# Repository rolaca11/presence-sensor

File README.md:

# Presence Sensor

A compact Zigbee presence sensor based on the Texas Instruments CC2340R5 microcontroller and a UART-connected mmWave radar module. Detects human presence and reports occupancy over Zigbee, with configurable detection parameters.

## Features

- **CC2340R5** - Low-power Zigbee microcontroller
- **mmWave radar sensor** - UART-connected presence detection module with configurable range, sensitivity, and latency
- **Zigbee End Device** - Occupancy Sensing cluster with custom attributes for remote sensor configuration
- **USB-C** - Power supply
- **Programming header** - 3-pin JST-SH connector for flashing firmware (compatible with Raspberry Pi Debug Probe)
- **3.3V LDO** - XC6206 voltage regulator
- **Factory reset button** - Hold on boot to clear network credentials
- **32.768 kHz & 48 MHz crystals** - For accurate timing and radio operation

## Project Structure

```
presence-sensor/
├── pcb/                    # KiCad 9 project files
│   ├── production/         # Manufacturing files (Gerbers, BOM, positions)
│   ├── footprints.pretty/  # Custom footprints
│   └── 3dmodels/           # 3D models for components
├── firmware/               # Zigbee firmware (CCS project, TI SimpleLink SDK)
├── enclosure/              # 3D printable enclosure (STEP + STL files)
└── LICENSE
```

## Firmware

The firmware is a Code Composer Studio project built on the TI SimpleLink Low Power F3 SDK. It implements a Zigbee End Device that:

- Reads presence data from the mmWave sensor over UART (9600 baud)
- Reports occupancy via the standard **Occupancy Sensing** cluster
- Sends **On/Off** commands to bound devices when presence state changes
- Exposes custom Zigbee attributes (`0xE000`–`0xE008`) for configuring the sensor remotely:

| Attribute | ID | Type | Description |
|-|-|-|-|
| Range Min | `0xE000` | uint16 | Minimum detection range (cm) |
| Range Max | `0xE001` | uint16 | Maximum detection range (cm) |
| Trigger Range | `0xE002` | uint16 | Trigger detection range (cm) |
| Trigger Sensitivity | `0xE003` | uint8 | Trigger sensitivity (0–9) |
| Keep Sensitivity | `0xE004` | uint8 | Keep sensitivity (0–9) |
| Trigger Delay | `0xE005` | uint8 | Trigger delay (x10ms) |
| Keep Timeout | `0xE006` | uint16 | Keep timeout (x500ms) |
| IO Polarity | `0xE007` | uint8 | Output pin polarity |
| Micromotion | `0xE008` | bool | Micromotion detection enable |

### Building

1. Install [Code Composer Studio](https://www.ti.com/tool/CCSTUDIO) v12.7+
2. Install the [SimpleLink Low Power F3 SDK](https://www.ti.com/tool/SIMPLELINK-LOWPOWER-SDK) v9.14+
3. Import the `firmware/` directory as a CCS project
4. Build and flash via the 3-pin SWD header using a compatible debug probe

## Manufacturing

Production files for PCB fabrication are located in `pcb/production/`:
- Gerber files (zipped)
- Bill of Materials (`bom.csv`)
- Pick and place positions (`positions.csv`)

The BOM includes LCSC part numbers for assembly at JLCPCB or similar services.

## Requirements

- [KiCad 9](https://www.kicad.org/) to view/edit the PCB design
- [Code Composer Studio](https://www.ti.com/tool/CCSTUDIO) v12.7+ to build the firmware
- [SimpleLink Low Power F3 SDK](https://www.ti.com/tool/SIMPLELINK-LOWPOWER-SDK) v9.14+
- 3D printer for the enclosure (optional)

## License

This project is licensed under the MIT License - see the [LICENSE](LICENSE) file for details.

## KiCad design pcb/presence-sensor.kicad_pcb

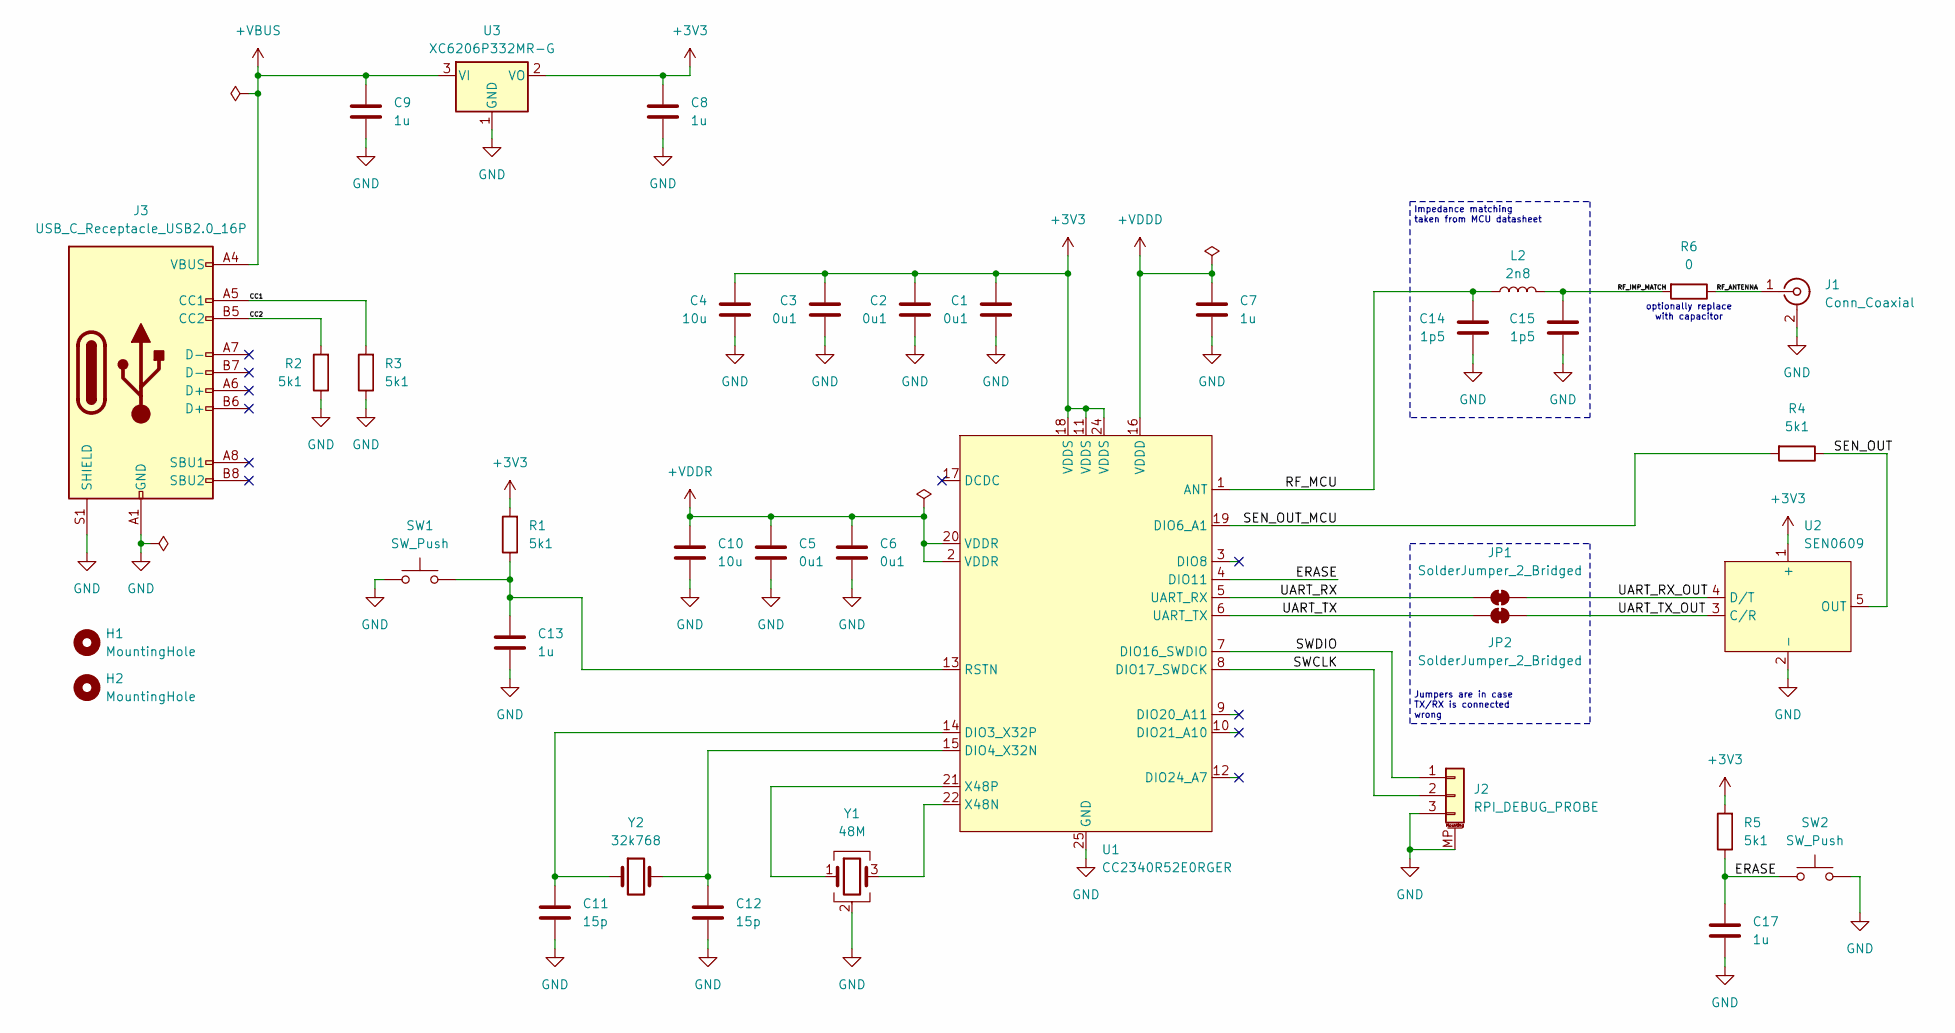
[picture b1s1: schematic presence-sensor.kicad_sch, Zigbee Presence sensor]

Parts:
C1, C2, C3, C5, C6: 0u1; C_0603_1608Metric; MPN CC0603KRX7R9BB104; JLCPCB Part # C14663
C4, C10: 10u; C_0603_1608Metric; MPN CL10A106KP8NNNC; JLCPCB Part # C19702
C7, C8, C9, C13, C17: 1u; C_0603_1608Metric; MPN CL10A105KB8NNNC; JLCPCB Part # C15849
C11, C12: 15p; C_0603_1608Metric; MPN CL10C150JB8NNNC; JLCPCB Part # C1644
C14, C15: 1p5; C_0603_1608Metric; MPN 0603CG1R5C500NT; JLCPCB Part # C1639
H1, H2: MountingHole; MountingHole_2.5mm
J1: Conn_Coaxial; Texas_SWRA117D_2.4GHz_Right
J2: RPI_DEBUG_PROBE; JST_SH_SM03B-SRSS-TB_1x03-1MP_P1.00mm_Horizontal; MPN SM03B-SRSS-TB(LF)(SN); JLCPCB Part # C160403
J3: USB_C_Receptacle_USB2.0_16P; USB_C_Receptacle_GCT_USB4105-xx-A_16P_TopMnt_Horizontal; MPN USB4105-GF-A-120; JLCPCB Part # C5184243
JP1, JP2: SolderJumper_2_Bridged; SolderJumper-2_P1.3mm_Bridged_RoundedPad1.0x1.5mm
L2: 2n8; L_0402_1005Metric; MPN SDCL1005C2N7STDF; JLCPCB Part # C27123
R1, R2, R3, R4, R5: 5k1; R_0603_1608Metric; MPN 0603WAF1003T5E; JLCPCB Part # C25803
R6: 0; R_0603_1608Metric; MPN 0603WAF0000T5E; JLCPCB Part # C21189
SW1, SW2: SW_Push; SW_SPST_B3U-1100P; MPN B3U-1100PM; JLCPCB Part # C6467298
U1: CC2340R52E0RGER; VQFN24_RGE-B_TEX; MPN CC2340R52E0RGER; JLCPCB Part # C20416850
U2: SEN0609; PinHeader_1x05_P2.54mm_Vertical
U3: XC6206P332MR-G; SOT-23-3; MPN XC6206P332MR-G; JLCPCB Part # C5446
Y1: 48M; Crystal_SMD_3225-4Pin_3.2x2.5mm; MPN XC32M4-48.000-F08NLDT; JLCPCB Part # C2925606
Y2: 32k768; Crystal_SMD_3215-2Pin_3.2x1.5mm; MPN Q13FC13500049; JLCPCB Part # C95361

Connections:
+3V3: C1.1, C2.1, C3.1, C4.1, C8.1, R1.2, R5.2, U1.11 (VDDS), U1.18 (VDDS), U1.24 (VDDS), U2.1 (+), U3.2 (VO)
+VBUS: C9.1, J3.A4 (VBUS), J3.A9 (VBUS), J3.B4 (VBUS), J3.B9 (VBUS), U3.3 (VI)
+VDDD: C7.1, U1.16 (VDDD)
+VDDR: C5.1, C6.1, C10.1, U1.2 (VDDR), U1.20 (VDDR)
/CC1: J3.A5 (CC1), R3.2
/CC2: J3.B5 (CC2), R2.2
/ERASE: C17.1, R5.1, SW2.1, U1.4 (DIO11)
/RF_ANTENNA: J1.1 (In), R6.1
/RF_IMP_MATCH: C15.1, L2.2, R6.2
/RF_MCU: C14.1, L2.1, U1.1 (ANT)
/SEN_OUT: R4.1, U2.5 (OUT)
/SEN_OUT_MCU: R4.2, U1.19 (DIO6_A1)
/SWCLK: J2.2, U1.8 (DIO17_SWDCK)
/SWDIO: J2.1, U1.7 (DIO16_SWDIO)
/UART_RX: JP1.1 (A), U1.5 (UART_RX)
/UART_RX_OUT: JP1.2 (B), U2.4 (D/T)
/UART_TX: JP2.1 (A), U1.6 (UART_TX)
/UART_TX_OUT: JP2.2 (B), U2.3 (C/R)
GND: C1.2, C2.2, C3.2, C4.2, C5.2, C6.2, C7.2, C8.2, C9.2, C10.2, C11.2, C12.2, C13.2, C14.2, C15.2, C17.2, J1.2 (Ext), J2.3, J2.MP (MountPin), J3.A1 (GND), J3.A12 (GND), J3.B1 (GND), J3.B12 (GND), J3.S1 (SHIELD), R2.1, R3.1, SW1.1, SW2.2, U1.23 (GND), U1.25 (GND), U2.2 (-), U3.1 (GND), Y1.2 (G), Y1.4 (G)
unnamed: C11.1, U1.14 (DIO3_X32P), Y2.1
unnamed: C12.1, U1.15 (DIO4_X32N), Y2.2
unnamed: C13.1, R1.1, SW1.2, U1.13 (RSTN)
unnamed: U1.22 (X48N), Y1.3
unnamed: U1.21 (X48P), Y1.1

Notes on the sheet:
Jumpers are in case TX/RX is connected wrong
optionally replace with capacitor
Impedance matching taken from MCU datasheet

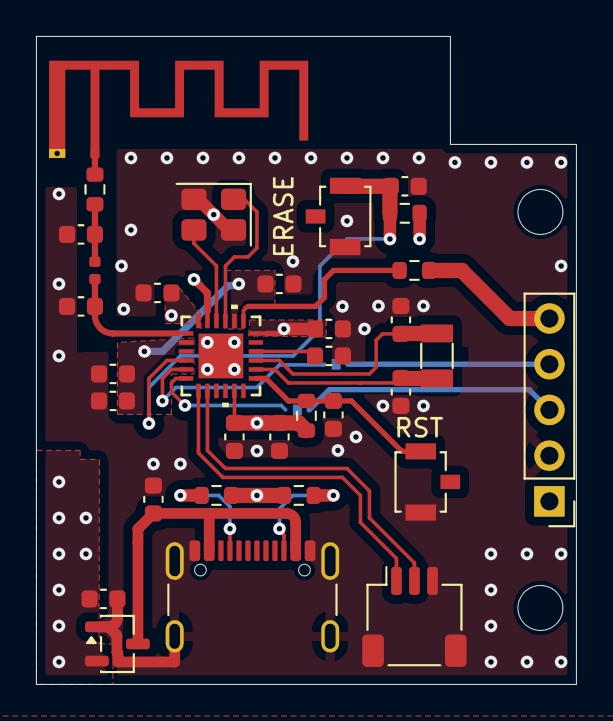
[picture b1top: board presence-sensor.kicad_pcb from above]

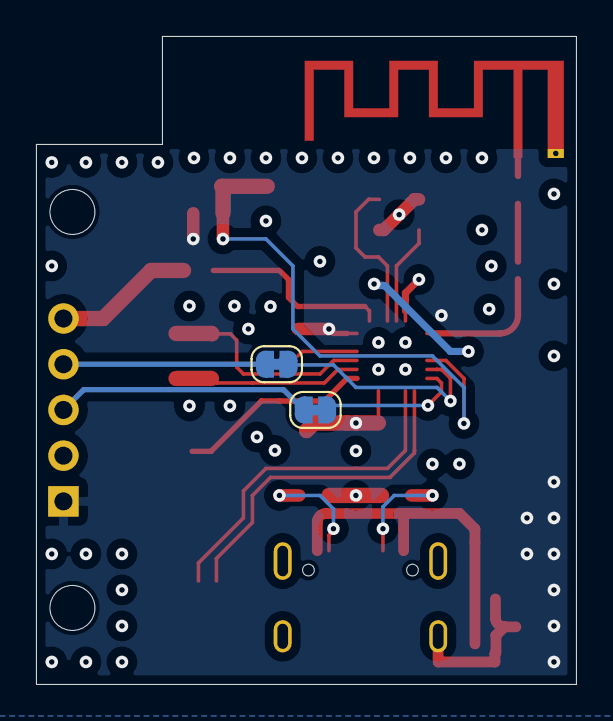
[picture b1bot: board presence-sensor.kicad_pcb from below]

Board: 4 copper layers, 30.0 x 36.0 mm, 37 parts (2 on the bottom side), 24 nets.

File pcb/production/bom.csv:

Designator,Footprint,Quantity,Value,LCSC Part #
"C1, C2, C3, C5, C6",0603,5,0u1,C14663
"C10, C4",0603,2,10u,C19702
"C11, C12",0603,2,15p,C1644
"C13, C17, C7, C8, C9",0603,5,1u,C15849
"C14, C15",0603,2,1p5,C1639
J2,JST_SH_SM03B-SRSS-TB_1x03-1MP_P1.00mm_Horizontal,1,RPI_DEBUG_PROBE,C160403
J3,USB_C_Receptacle_GCT_USB4105-xx-A_16P_TopMnt_Horizontal,1,USB_C_Receptacle_USB2.0_16P,C5184243
L2,0402,1,2n8,C27123
"R1, R2, R3, R4, R5",0603,5,5k1,C25803
R6,0603,1,0,C21189
"SW1, SW2",SW_SPST_B3U-1100P,2,SW_Push,C6467298
U1,VQFN24_RGE-B_TEX,1,CC2340R52E0RGER,C20416850
U3,SOT-23-3,1,XC6206P332MR-G,C5446
Y1,Crystal_SMD_3225-4Pin_3.2x2.5mm,1,48M,C2925606
Y2,Crystal_SMD_3215-2Pin_3.2x1.5mm,1,32k768,C95361

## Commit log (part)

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2026-01-18 rework VDDR and ERASE button
2026-01-18 rev 0.1
2026-01-18 part details
2026-01-18 organize files
2026-01-18 reorganize kicad project
2026-01-18 fix grounding, update fabrication files
2026-01-18 finalize files
2026-01-18 Order placed
2026-01-18 add STL files
2026-02-14 firmware
2026-02-14 what
2026-02-14 for real this time
